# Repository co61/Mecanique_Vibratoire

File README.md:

# Mecanique_Vibratoire
Conception d'un banc de mesure de flexion sur une lame 
Merci de parcourir les différents dossier pour y découvrir les Rapports asociés

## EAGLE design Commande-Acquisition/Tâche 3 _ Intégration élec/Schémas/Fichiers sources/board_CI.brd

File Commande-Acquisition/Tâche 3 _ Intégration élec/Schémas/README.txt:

~~~ extension ~~~~~~~~~~~~~ logiciel ~~~~~~~~~~~~~~~~~ Remarques ~~~~~~~~~~~~~~~~~~~~~~~~~~~~~~~~~~~~~~

      .qet		  QElectroTech		    Ajouter les fichiers "Elements nécessaires..."
      .brd		  Eagle
      .sch		  Eagle
      .f3z		  Autodesk fusion 360       Archive comprenant le .brd et le .sch liés entre eux

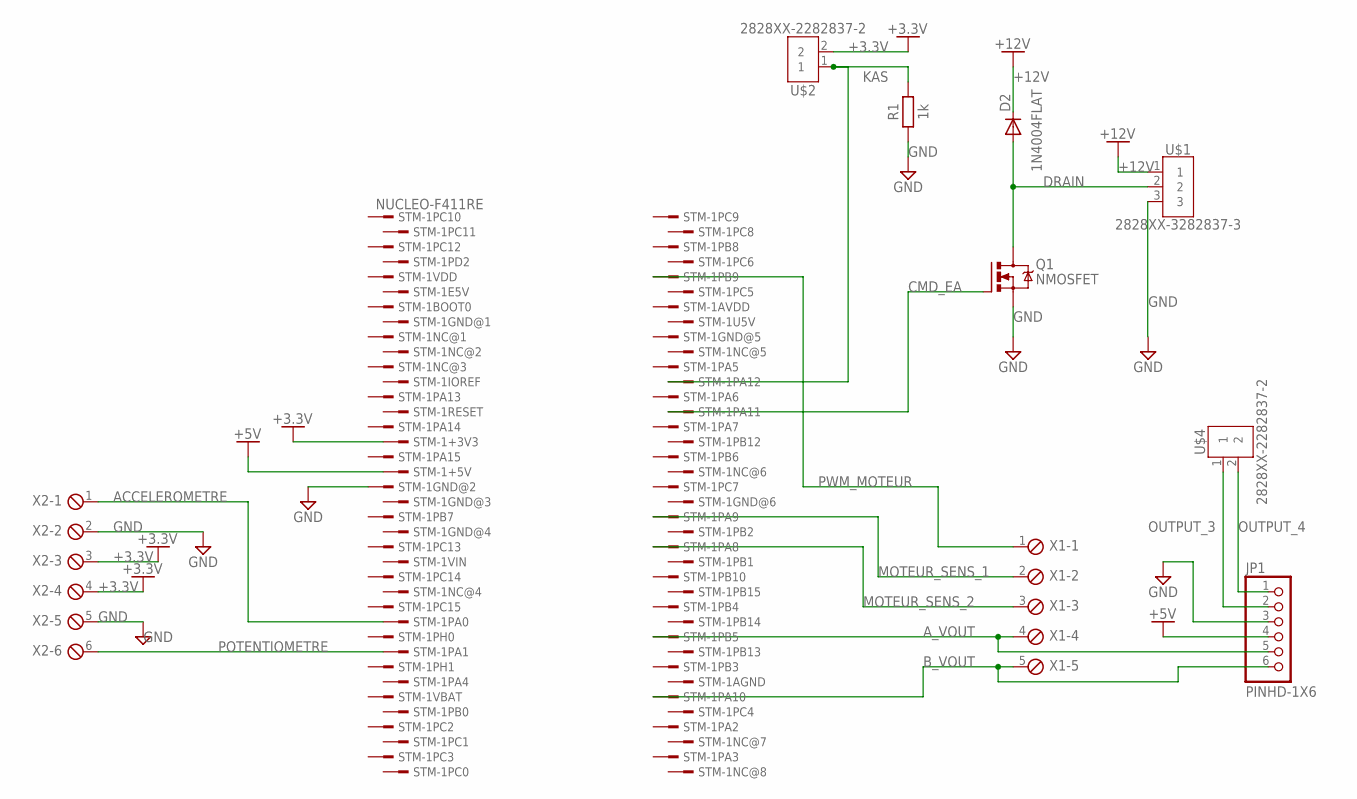
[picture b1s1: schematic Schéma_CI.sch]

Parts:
D2: 1N4004FLAT; DO41-10
JP1: PINHD-1X6; 1X06
Q1: NMOSFET; TO220BV
R1: 1k; RESAD724W46L381D178B
STM-1: NUCLEO-F411RE; CONN_STM32_NUCLEO
U$1: 2828XX-3282837-3; TERMBLK_508-3N
U$2, U$4: 2828XX-2282837-2; TERMBLK_508-2N
X1: MPT5; 5POL254
X2: MPT6; 6POL254

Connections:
+3.3V: STM-1.16, U$2.2, X2.3, X2.4
+5V: JP1.4, STM-1.18
+12V: D2.C, U$1.1
ACCELEROMETRE: STM-1.28, X2.1
A_VOUT: JP1.5, STM-1.67, X1.4
B_VOUT: JP1.6, STM-1.71, X1.5
CMD_EA: Q1.G, STM-1.52
DRAIN: D2.A, Q1.D, U$1.2
GND: JP1.3, Q1.S, R1.1, STM-1.19, U$1.3, X2.2, X2.5
KAS: R1.2, STM-1.50, U$2.1
MOTEUR_SENS_1: STM-1.59, X1.2
MOTEUR_SENS_2: STM-1.61, X1.3
OUTPUT_3: JP1.2, U$4.1
OUTPUT_4: JP1.1, U$4.2
POTENTIOMETRE: STM-1.30, X2.6
PWM_MOTEUR: STM-1.43, X1.1

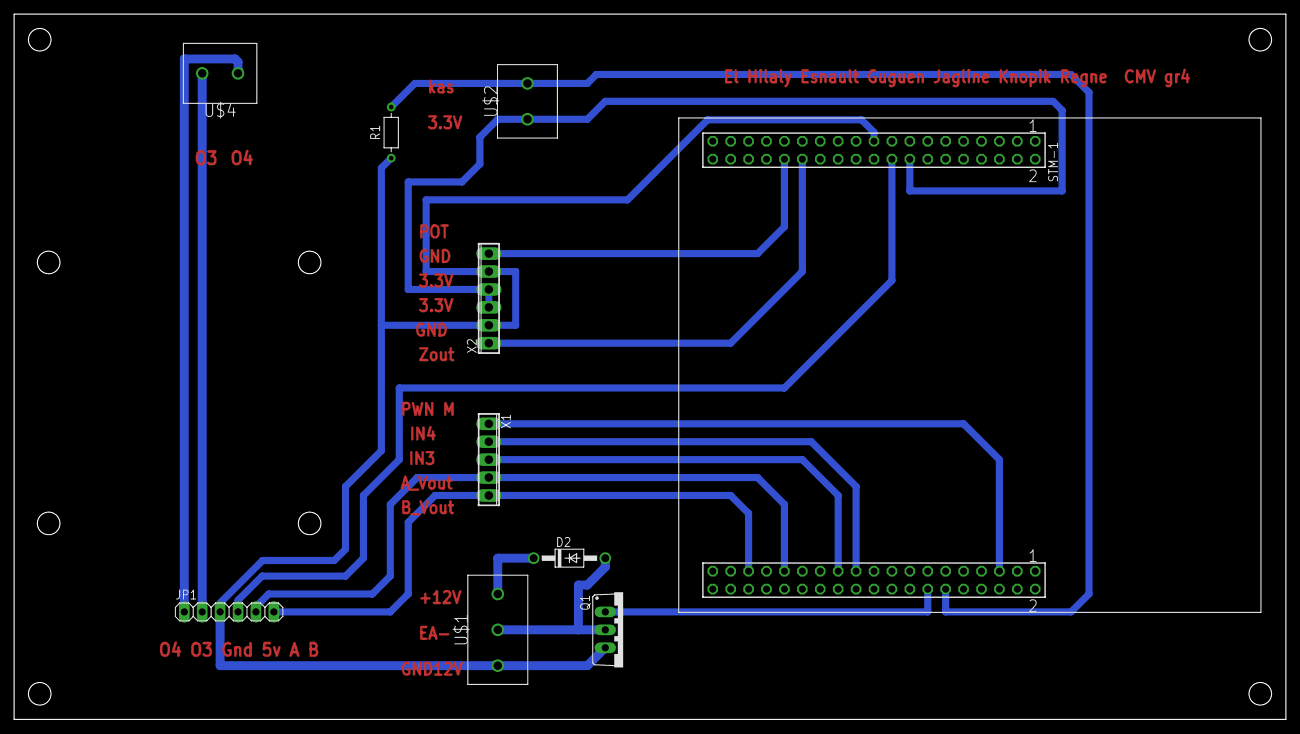
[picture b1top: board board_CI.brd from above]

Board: 2 copper layers, 180.3 x 100.0 mm, 10 parts (0 on the bottom side), 16 nets.

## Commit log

2021-12-14 Adding project CMV finished for storing
